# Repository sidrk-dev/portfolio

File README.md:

# Portfolio - Siddharth Rajasekaran

This is a personal engineering portfolio website built with **Next.js 15**, **Tailwind CSS**, and **Framer Motion**.

## Design System
- **Dark Theme Only**: Background `#0a0a0a`.
- **Primary Color**: Electric Blue (`#3B82F6`) to Cyan (`#06B6D4`) gradients.
- **Typography**: Inter (Body), Space Grotesk (Headings).
- **Style**: Glassmorphism, animated circuit board particles, glowing effects.

## Features
- **Hero**: Split-text name reveal and text-scramble role cycle.
- **About**: Animated statistics.
- **Projects**: Data-driven project cards with hover effects.
- **Skills**: Categorized skill badges.
- **Experience**: Vertical timeline with glowing nodes.
- **Contact**: Simple social links.

## Getting Started

1. **Install dependencies**:
   ```bash
   npm install
   ```

2. **Run the development server**:
   ```bash
   npm run dev
   ```
   Open [http://localhost:3000](http://localhost:3000) to view it in the browser.

3. **Build for production**:
   ```bash
   npm run build
   ```

## Customization
- Update content in `src/data/portfolio.ts`.
- Adjust styles in `src/app/globals.css`.

## Deployment
This project is optimized for deployment on **Vercel**.
1. Push to GitHub.
2. Import project in Vercel.
3. Deploy.

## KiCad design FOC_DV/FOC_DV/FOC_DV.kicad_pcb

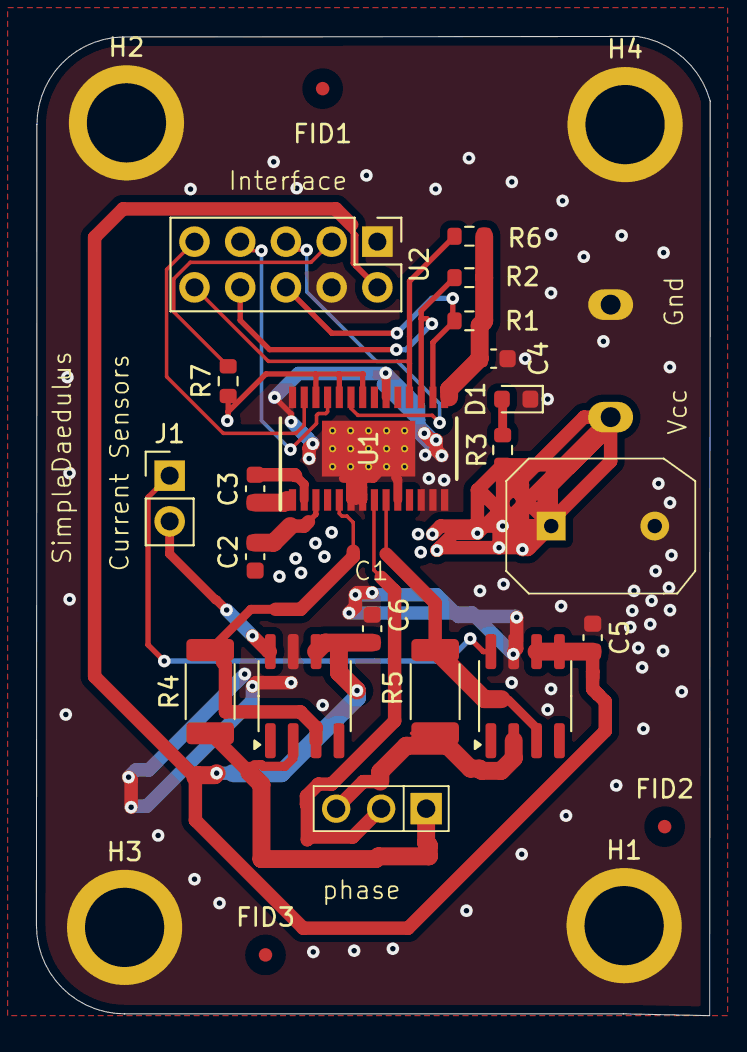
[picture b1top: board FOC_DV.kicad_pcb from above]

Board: 2 copper layers, 37.4 x 54.4 mm, 27 parts (0 on the bottom side), 23 nets.

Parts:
C1: 100uF; circular_cap_6.3
C2, C3: 100nF; C_0603_1608Metric
C4: 470nF; C_0603_1608Metric
C5, C6: 1uF; C_0603_1608Metric
D1: LED; LED_0603_1608Metric
FID1, FID2, FID3: Fiducial; Fiducial_0.75mm_Mask2.25mm
H1, H2, H3, H4: MountingHole; MountingHole_3.2mm_M3_Pad_Via
J1: Conn_01x02; PinHeader_1x02_P2.54mm_Vertical
J3: TB001-500-03BE; phase_pinouts
R1, R2, R6, R7: 10k; R_0603_1608Metric
R3: 1k; R_0603_1608Metric
R4: 10m; R_2010_5025Metric
R5: 10k; R_2010_5025Metric
U1: DRV8313PWP; PWP0028F_L
U2: PinHeader_2x05_P2.54mm_Vertical
U3, U4: INA240A2D; SOIC-8_3.9x4.9mm_P1.27mm

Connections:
+3.3INTRN: C4.2, R1.1, R2.1, R6.2, U1.15 (V3P3)
+3.3V: C5.1, C6.1, U2.2, U3.5, U3.6 (V+), U4.5, U4.6 (V+)
CA_out: J1.2, U3.8 (+)
CC_out: J1.1, U4.8 (+)
EN: R7.2, U1.22 (EN3), U1.24 (EN2), U1.26 (EN1)
GND: C1.2, C4.1, C5.2, C6.2, D1.1 (K), H1.1, H2.1, H3.1, H4.1, U1.6 (PGND1), U1.7 (PGND2), U1.10 (PGND3), U1.12 (COMPP), U1.13 (COMPN), U1.14 (GND), U1.20 (GND), U1.28 (GND), U1.29 (EXP), U1.V, U2.1, U2.4, U3.7 (REF1), U4.7 (REF1)
IN1: U1.27 (IN1), U2.9
IN2: U1.25 (IN2), U2.7
IN3: U1.23 (IN3), U2.5
unnamed: D1.2 (A), R3.2
unnamed: C3.1, U1.2 (CPH)
unnamed: C3.2, U1.1 (CPL)
unnamed: C2.1, U1.3 (VCP)
unnamed: R7.1, U2.3
PH_CS_A: R4.2, U1.5 (OUT1), U3.3 (REF2)
PH_CS_C: R5.2, U1.9 (OUT3), U4.3 (REF2)
VCC: C1.1, C2.2, R3.1, U1.4 (VM), U1.11 (VM)
nFLT: R6.1, U1.18 (~FAULT), U2.10
nRST: R1.2, U1.16 (~RESET), U2.6
nSLP: R2.2, U1.17 (~SLEEP), U2.8
phase_A: J3.3, R4.1, U3.2 (GND), U3.4 (GND)
phase_B: J3.2, U1.8 (OUT2)
phase_C: J3.1, R5.1, U4.2 (GND), U4.4 (GND)

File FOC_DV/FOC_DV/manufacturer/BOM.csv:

Designator,Value,Footprint,Qauntity,DNP,Manufacturer,Manufactrer Part Number,LCSC
D1,LED,LED_SMD:LED_0603_1608Metric,1,,YONGYUTAI,YLED0603R,C19171390
"R4,R5",10m,Resistor_SMD:R_2010_5025Metric,2,,YAGEO,RC2010JK-0710ML,C4323757
"C5,C6",1uF,Capacitor_SMD:C_0603_1608Metric,2,,KEMET,C0603C105K3PACTU,C2167338
"U3,U4",INA240A2D,Package_SO:SOIC-8_3.9x4.9mm_P1.27mm,2,,Texas Instruments,INA240A2DR,C2060768
R3,1k,Resistor_SMD:R_0603_1608Metric,1,,YAGEO,RC0603JR-7W1KL,C859124
"R1,R2,R6,R7",10k,Resistor_SMD:R_0603_1608Metric,4,,YAGEO,RC0603FR-1310KL,C845630
C4,470nF,Capacitor_SMD:C_0603_1608Metric,1,,YAGEO,CC0603ZRY5V6BB474,C327269
C1,100uF,simpleFOC:circular_cap_6.3,1,,Vertical Technology,VT1V101M-CRE77,C294520
U1,DRV8313PWP,simpleFOC:PWP0028F_L,1,,Texas Instruments,DRV8313PWPR,C92482
"C2,C3",100nF,Capacitor_SMD:C_0603_1608Metric,2,,SAMSUNG,CL10B104KB8NNNC,C1591
U2,~,Connector_PinHeader_2.54mm:PinHeader_2x05_P2.54mm_Vertical,1,DNP,,,
J3,TB001-500-03BE,simpleFOC:phase_pinouts,1,DNP,CUI,,
J2,TB002V-500-02BE,simpleFOC:VCCpad,1,DNP,CUI,,
J1,Conn_01x02,Connector_PinHeader_2.54mm:PinHeader_1x02_P2.54mm_Vertical,1,DNP,,,

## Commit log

2025-06-22 fix issues
2025-06-22 Deploy to GitHub Pages
2026-02-18 Re-initializing project root
2026-02-18 Fix build: ProjectPage server component and generateStaticParams
2026-02-18 Update GitHub and LinkedIn links
2026-02-19 Update BLDC actuator writeup with detailed blog content
2026-02-20 feat: integrate motor characterization blog post
2026-02-26 feat: mobile layout optimization, remove em dashes, add FOC PCB debugging blog post
2026-02-26 fix: correct technical inaccuracies in FOC PCB driver writeup
2026-02-26 feat: move blog posts to .md files, add YouTube embed support via ::youtube[ID]
2026-03-02 feat: rewrite project writeups, add KiCad schematic, kicanvas embed
    - Rewrote bldc-actuator.md: at-a-glance table, voice fix, hardware credibility, what I'd do differently section, removed redundant GitHub line
    - Rewrote foc-driver.md: PCB design section from schematic, inline current sensing section (INA240A2D 50V/V), outcome paragraph
    - Added FOC_DV KiCad project files to repo
    - Added remarkKiCanvas plugin to project page renderer
    - Updated portfolio.ts FOC driver tags (INA240, Current Sensing)
2026-03-02 feat: custom interactive SVG schematic viewer for foc-driver page
2026-03-02 fix: full-width layout, top metadata bar, static schematic image, tighter prose
